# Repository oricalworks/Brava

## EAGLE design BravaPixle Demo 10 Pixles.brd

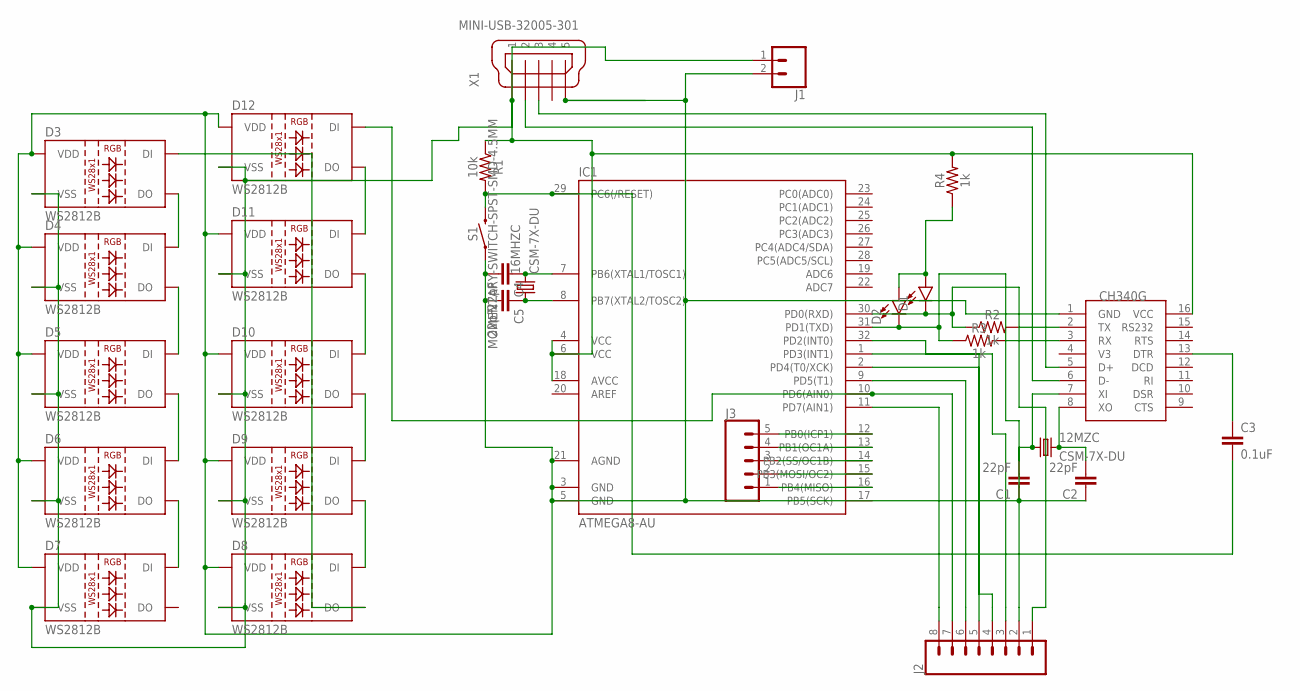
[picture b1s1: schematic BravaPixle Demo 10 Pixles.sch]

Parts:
12MZC, 16MHZC: CSM-7X-DU
C1, C2, C4, C5: 22pF; 0603
C3: 0.1uF; 0603
D1, D2: LED0603; LED-0603
D3, D4, D5, D6, D7, D8, D9, D10, D11, D12: WS2812B
IC1: ATMEGA8-AU; TQFP32-08
J1: CONN_02PTH3; 1X02_LONGPADS
J2: CONN_08LOCK_LONGPADS; 1X08_LOCK_LONGPADS
J3: CONN_05; 1X05
R1: 10k; 0603
R2, R3, R4: 1k; 0603
S1: MOMENTARY-SWITCH-SPST-SMD-4.5MM; TACTILE_SWITCH_SMD_4.5MM
U$1: CH340G; SOIC16
X1: MINI-USB-32005-301; 32005-301

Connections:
unnamed: C3.2, IC1.29 (PC6(/RESET)), R1.2, S1.1 (2), S1.4 (2)
unnamed: D11.4 (DI), D12.2 (DO)
unnamed: D1.C, IC1.30 (PD0(RXD)), J2.1, R2.1
unnamed: D10.4 (DI), D11.2 (DO)
unnamed: D2.C, IC1.31 (PD1(TXD)), J2.2, R3.1
unnamed: R2.2, U$1.2 (TX)
unnamed: R3.2, U$1.3 (RX)
unnamed: U$1.6 (D-), X1.2
unnamed: U$1.5 (D+), X1.3
unnamed: D1.A, D2.A, R4.1
unnamed: 12MZC.2, C2.2, U$1.8 (XO)
unnamed: 12MZC.1, C1.2, U$1.7 (XI)
unnamed: D9.4 (DI), D10.2 (DO)
unnamed: C3.1, U$1.13 (DTR)
unnamed: D8.4 (DI), D9.2 (DO)
unnamed: D3.3 (VSS), D4.3 (VSS), D5.3 (VSS), D6.3 (VSS), D7.3 (VSS), D8.3 (VSS), D9.3 (VSS), D10.3 (VSS), D11.3 (VSS), D12.3 (VSS), IC1.4 (VCC), IC1.6 (VCC), IC1.18 (AVCC), J1.1, R1.1, R4.2, U$1.16 (VCC), X1.1
unnamed: C1.1, C2.1, C4.2, C5.2, D3.1 (VDD), D4.1 (VDD), D5.1 (VDD), D6.1 (VDD), D7.1 (VDD), D8.1 (VDD), D9.1 (VDD), D10.1 (VDD), D11.1 (VDD), D12.1 (VDD), IC1.3 (GND), IC1.5 (GND), IC1.21 (AGND), J1.2, S1.2 (1), S1.3 (1), U$1.1 (GND), X1.5
unnamed: D3.2 (DO), D4.4 (DI)
unnamed: D4.2 (DO), D5.4 (DI)
unnamed: D5.2 (DO), D6.4 (DI)
unnamed: D6.2 (DO), D7.4 (DI)
unnamed: D3.4 (DI), D8.2 (DO)
unnamed: D12.4 (DI), IC1.10 (PD6(AIN0)), J2.7
unnamed: IC1.12 (PB0(ICP1)), J3.5
unnamed: IC1.32 (PD2(INT0)), J2.3
unnamed: IC1.1 (PD3(INT1)), J2.4
unnamed: IC1.2 (PD4(T0/XCK)), J2.5
unnamed: IC1.9 (PD5(T1)), J2.6
unnamed: IC1.11 (PD7(AIN1)), J2.8
unnamed: IC1.13 (PB1(OC1A)), J3.4
unnamed: IC1.14 (PB2(SS/OC1B)), J3.3
unnamed: IC1.15 (PB3(MOSI/OC2)), J3.2
unnamed: IC1.16 (PB4(MISO)), J3.1
unnamed: 16MHZC.2, C4.1, IC1.7 (PB6(XTAL1/TOSC1))
unnamed: 16MHZC.1, C5.1, IC1.8 (PB7(XTAL2/TOSC2))

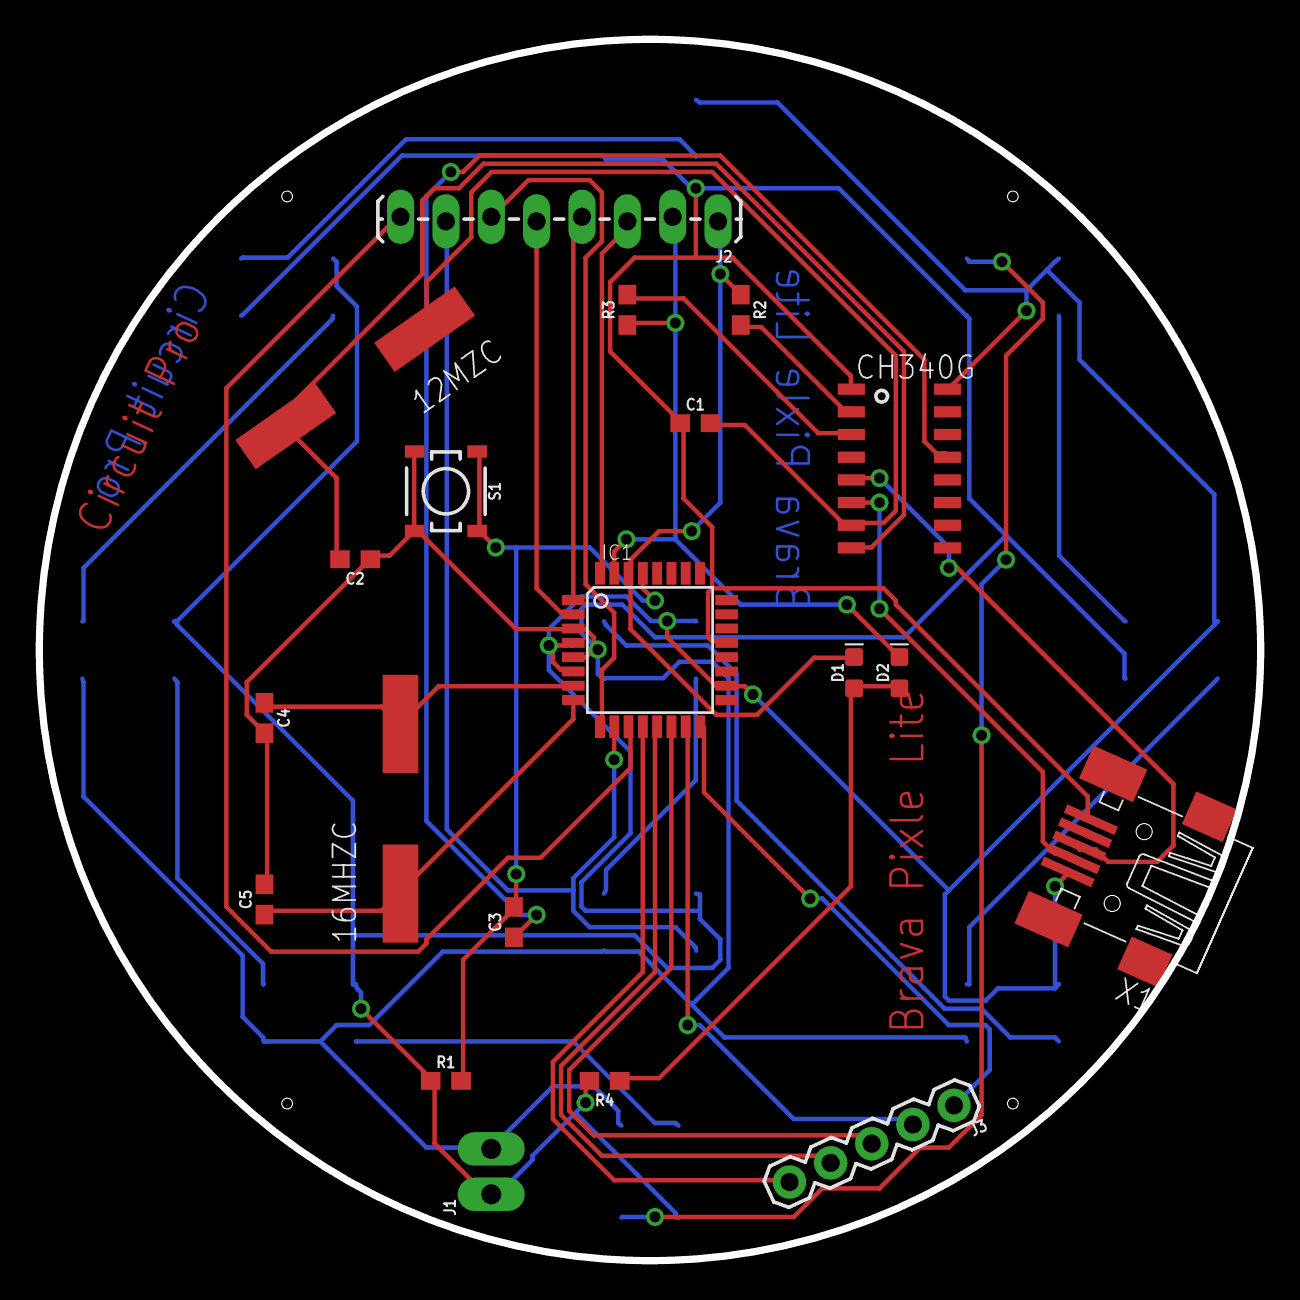
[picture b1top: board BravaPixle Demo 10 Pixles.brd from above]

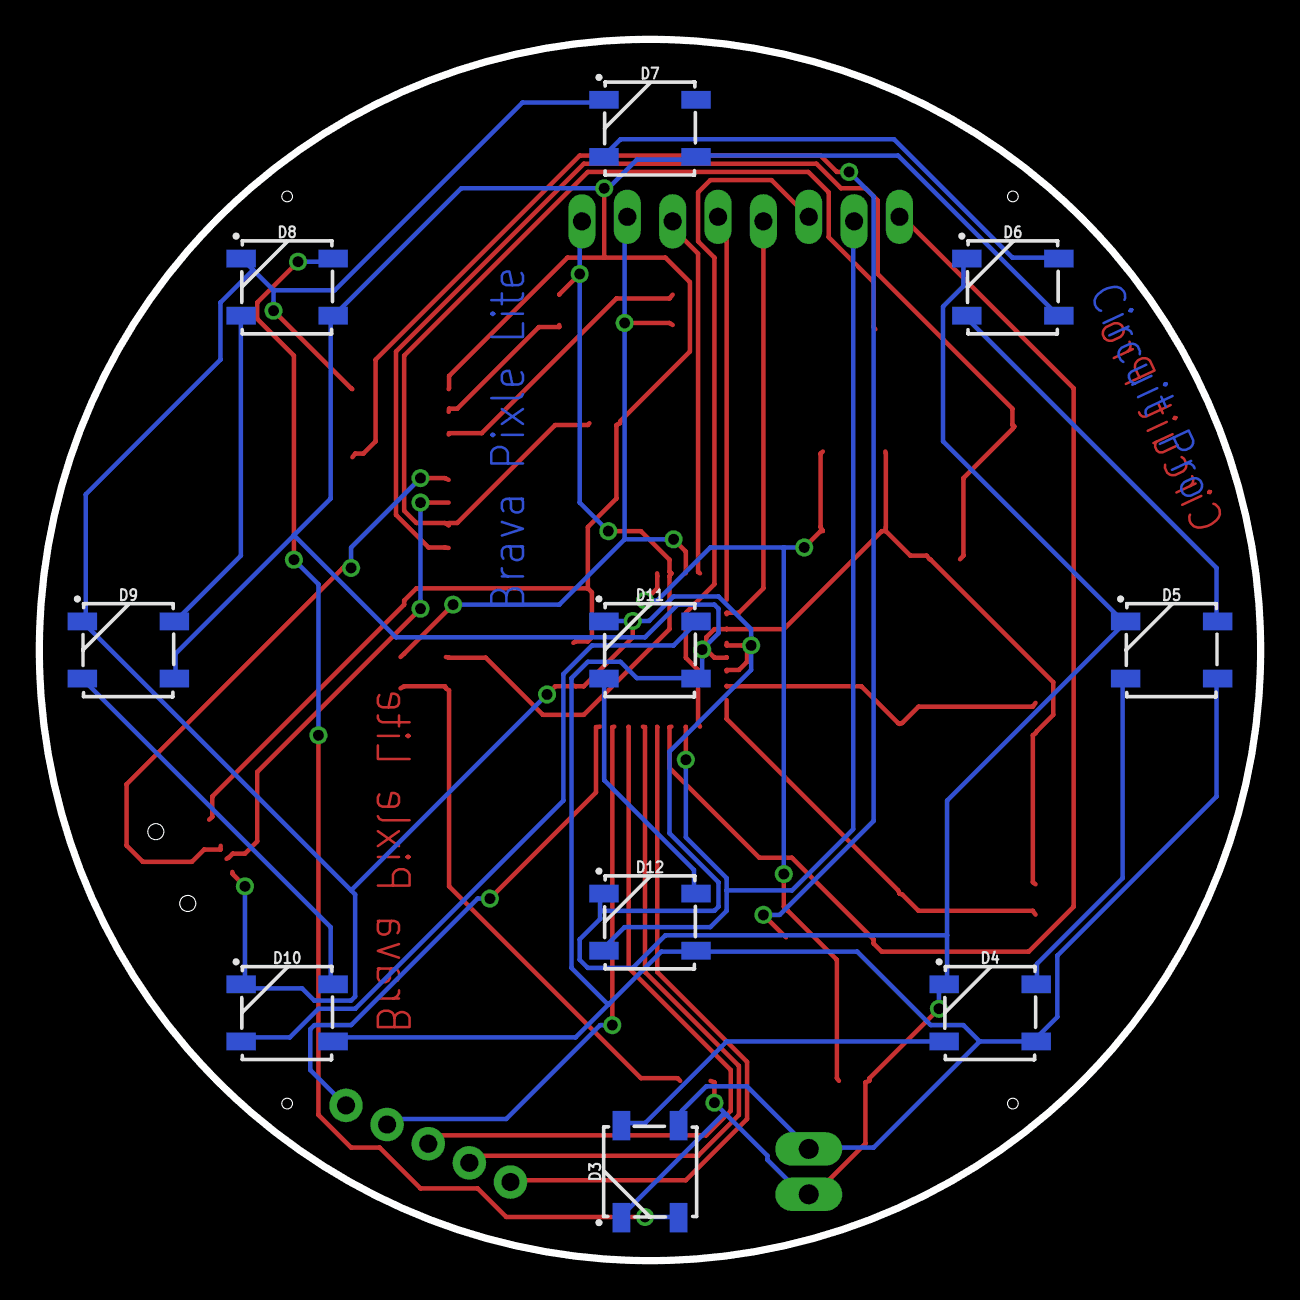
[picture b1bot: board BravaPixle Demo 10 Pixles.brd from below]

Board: 2 copper layers, 68.4 x 68.4 mm, 30 parts (10 on the bottom side), 35 nets.

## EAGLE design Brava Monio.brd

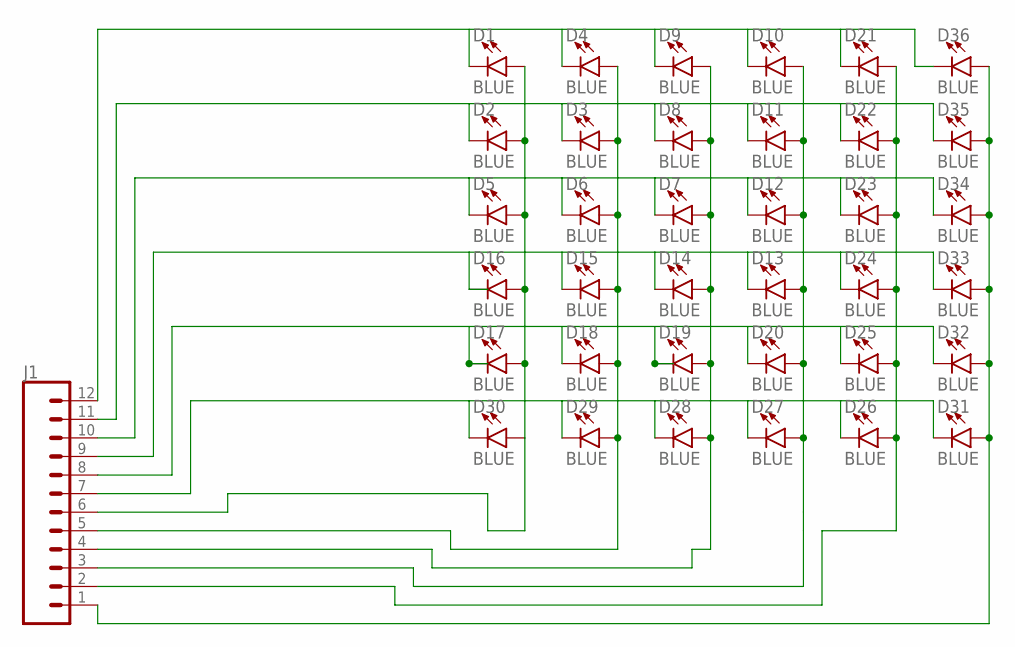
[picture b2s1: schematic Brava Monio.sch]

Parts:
D1, D2, D3, D4, D5, D6, D7, D8, D9, D10, D11, D12, D13, D14, D15, D16, D17, D18, D19, D20, D21, D22, D23, D24, D25, D26, D27, D28, D29, D30, D31, D32, D33, D34, D35, D36: BLUE; LED-0603
J1: CONN_12LONGPADS; 1X12_LONGPADS

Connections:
unnamed: D1.A, D2.A, D5.A, D16.A, D17.A, D30.A, J1.6
unnamed: D3.A, D4.A, D6.A, D15.A, D18.A, D29.A, J1.5
unnamed: D7.A, D8.A, D9.A, D14.A, D19.A, D28.A, J1.4
unnamed: D10.A, D11.A, D12.A, D13.A, D20.A, D27.A, J1.3
unnamed: D21.A, D22.A, D23.A, D24.A, D25.A, D26.A, J1.2
unnamed: D31.A, D32.A, D33.A, D34.A, D35.A, D36.A, J1.1
unnamed: D1.C, D4.C, D9.C, D10.C, D21.C, D36.C, J1.12
unnamed: D2.C, D3.C, D8.C, D11.C, D22.C, D35.C, J1.11
unnamed: D5.C, D6.C, D7.C, D12.C, D23.C, D34.C, J1.10
unnamed: D13.C, D14.C, D15.C, D16.C, D24.C, D33.C, J1.9
unnamed: D17.C, D18.C, D19.C, D20.C, D25.C, D32.C, J1.8
unnamed: D26.C, D27.C, D28.C, D29.C, D30.C, D31.C, J1.7

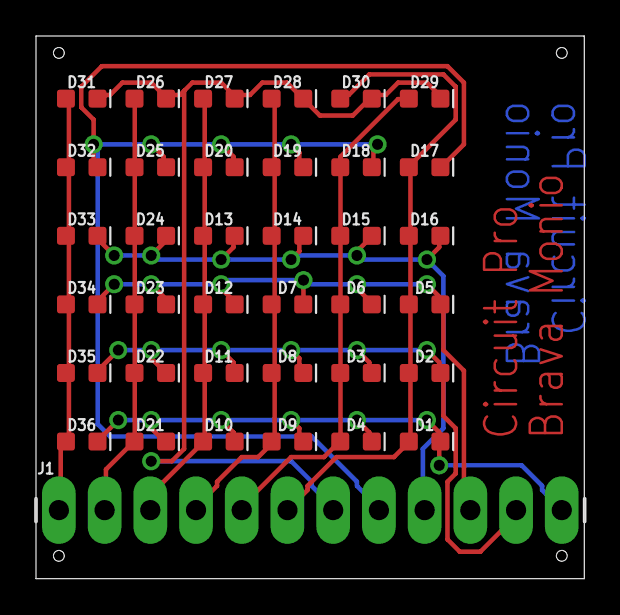
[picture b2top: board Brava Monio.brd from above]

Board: 2 copper layers, 30.5 x 30.1 mm, 37 parts (0 on the bottom side), 12 nets.

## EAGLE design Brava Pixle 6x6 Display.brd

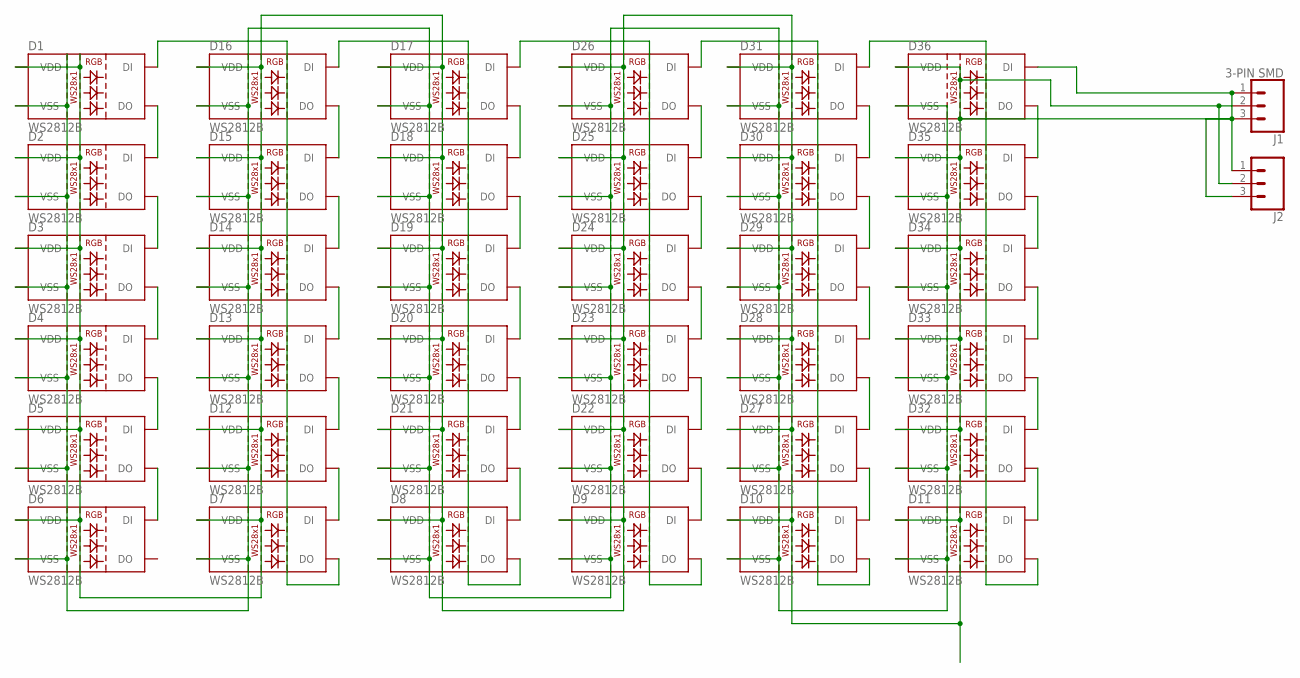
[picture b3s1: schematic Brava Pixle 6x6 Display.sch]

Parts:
D1, D2, D3, D4, D5, D6, D7, D8, D9, D10, D11, D12, D13, D14, D15, D16, D17, D18, D19, D20, D21, D22, D23, D24, D25, D26, D27, D28, D29, D30, D31, D32, D33, D34, D35, D36: WS2812B
J1: 3-PIN SMD; JST-3-SMD
J2: CONN_03LONGPADS; 1X03_LONGPADS

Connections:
unnamed: D1.1 (VDD), D2.1 (VDD), D3.1 (VDD), D4.1 (VDD), D5.1 (VDD), D6.1 (VDD), D7.1 (VDD), D8.1 (VDD), D9.1 (VDD), D10.1 (VDD), D11.1 (VDD), D12.1 (VDD), D13.1 (VDD), D14.1 (VDD), D15.1 (VDD), D16.1 (VDD), D17.1 (VDD), D18.1 (VDD), D19.1 (VDD), D20.1 (VDD), D21.1 (VDD), D22.1 (VDD), D23.1 (VDD), D24.1 (VDD), D25.1 (VDD), D26.1 (VDD), D27.1 (VDD), D28.1 (VDD), D29.1 (VDD), D30.1 (VDD), D31.1 (VDD), D32.1 (VDD), D33.1 (VDD), D34.1 (VDD), D35.1 (VDD), D36.1 (VDD), J1.2, J1.3, J2.2, J2.3
unnamed: D1.3 (VSS), D2.3 (VSS), D3.3 (VSS), D4.3 (VSS), D5.3 (VSS), D6.3 (VSS), D7.3 (VSS), D8.3 (VSS), D9.3 (VSS), D10.3 (VSS), D11.3 (VSS), D12.3 (VSS), D13.3 (VSS), D14.3 (VSS), D15.3 (VSS), D16.3 (VSS), D17.3 (VSS), D18.3 (VSS), D19.3 (VSS), D20.3 (VSS), D21.3 (VSS), D22.3 (VSS), D23.3 (VSS), D24.3 (VSS), D25.3 (VSS), D26.3 (VSS), D27.3 (VSS), D28.3 (VSS), D29.3 (VSS), D30.3 (VSS), D31.3 (VSS), D32.3 (VSS), D33.3 (VSS), D34.3 (VSS), D35.3 (VSS), D36.3 (VSS)
unnamed: D36.4 (DI), J1.1, J2.1
unnamed: D35.4 (DI), D36.2 (DO)
unnamed: D34.4 (DI), D35.2 (DO)
unnamed: D33.4 (DI), D34.2 (DO)
unnamed: D32.4 (DI), D33.2 (DO)
unnamed: D11.4 (DI), D32.2 (DO)
unnamed: D11.2 (DO), D31.4 (DI)
unnamed: D30.4 (DI), D31.2 (DO)
unnamed: D29.4 (DI), D30.2 (DO)
unnamed: D28.4 (DI), D29.2 (DO)
unnamed: D27.4 (DI), D28.2 (DO)
unnamed: D10.4 (DI), D27.2 (DO)
unnamed: D10.2 (DO), D26.4 (DI)
unnamed: D25.4 (DI), D26.2 (DO)
unnamed: D24.4 (DI), D25.2 (DO)
unnamed: D23.4 (DI), D24.2 (DO)
unnamed: D22.4 (DI), D23.2 (DO)
unnamed: D9.4 (DI), D22.2 (DO)
unnamed: D9.2 (DO), D17.4 (DI)
unnamed: D17.2 (DO), D18.4 (DI)
unnamed: D18.2 (DO), D19.4 (DI)
unnamed: D19.2 (DO), D20.4 (DI)
unnamed: D20.2 (DO), D21.4 (DI)
unnamed: D8.4 (DI), D21.2 (DO)
unnamed: D8.2 (DO), D16.4 (DI)
unnamed: D15.4 (DI), D16.2 (DO)
unnamed: D14.4 (DI), D15.2 (DO)
unnamed: D13.4 (DI), D14.2 (DO)
unnamed: D12.4 (DI), D13.2 (DO)
unnamed: D7.4 (DI), D12.2 (DO)
unnamed: D1.4 (DI), D7.2 (DO)
unnamed: D1.2 (DO), D2.4 (DI)
unnamed: D2.2 (DO), D3.4 (DI)
unnamed: D3.2 (DO), D4.4 (DI)
unnamed: D4.2 (DO), D5.4 (DI)
unnamed: D5.2 (DO), D6.4 (DI)

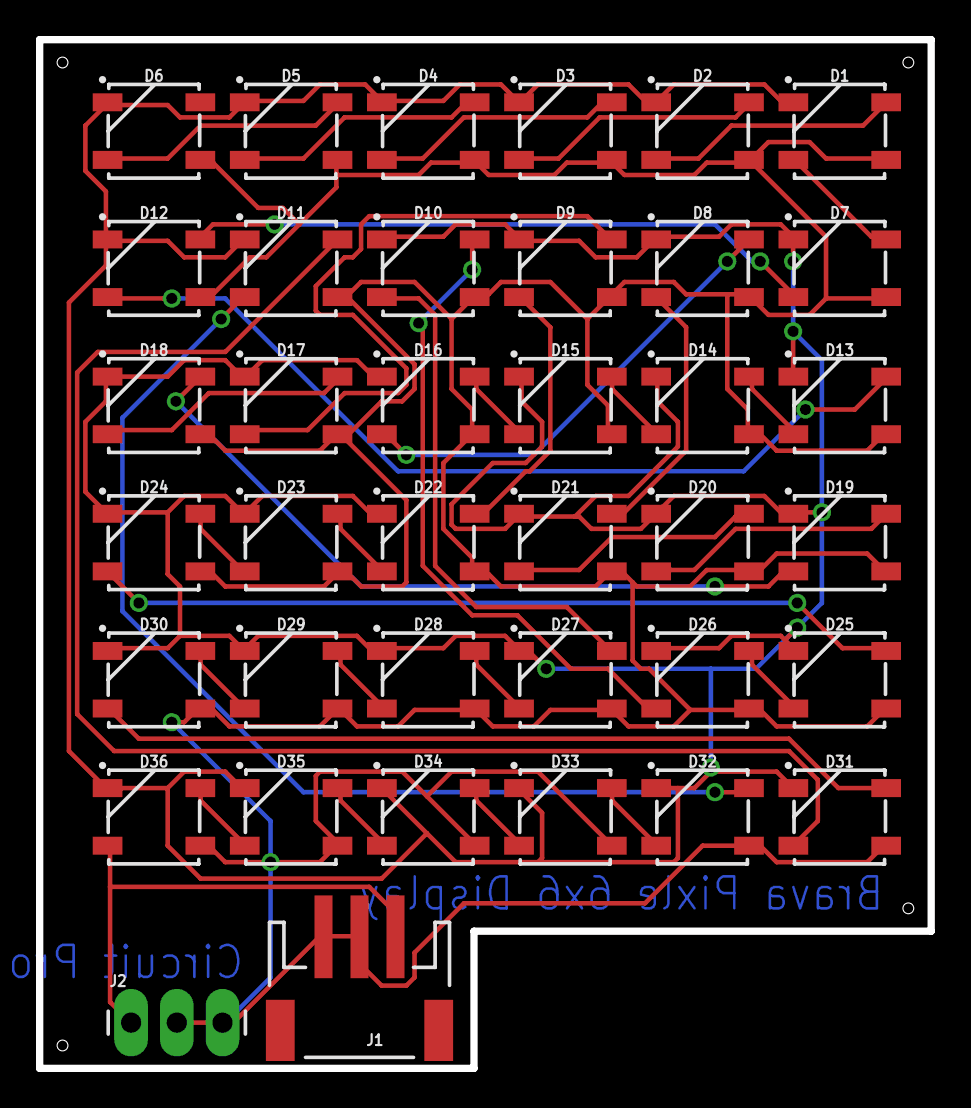
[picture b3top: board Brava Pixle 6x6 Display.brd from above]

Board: 2 copper layers, 49.5 x 57.1 mm, 38 parts (0 on the bottom side), 38 nets.

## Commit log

2017-05-24 First Release!!

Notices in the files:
parts and their libraries:
SparkFun-LED: Licensing: Creative Commons ShareAlike 4.0 International - https://creativecommons.org/licenses/by-sa/4.0
